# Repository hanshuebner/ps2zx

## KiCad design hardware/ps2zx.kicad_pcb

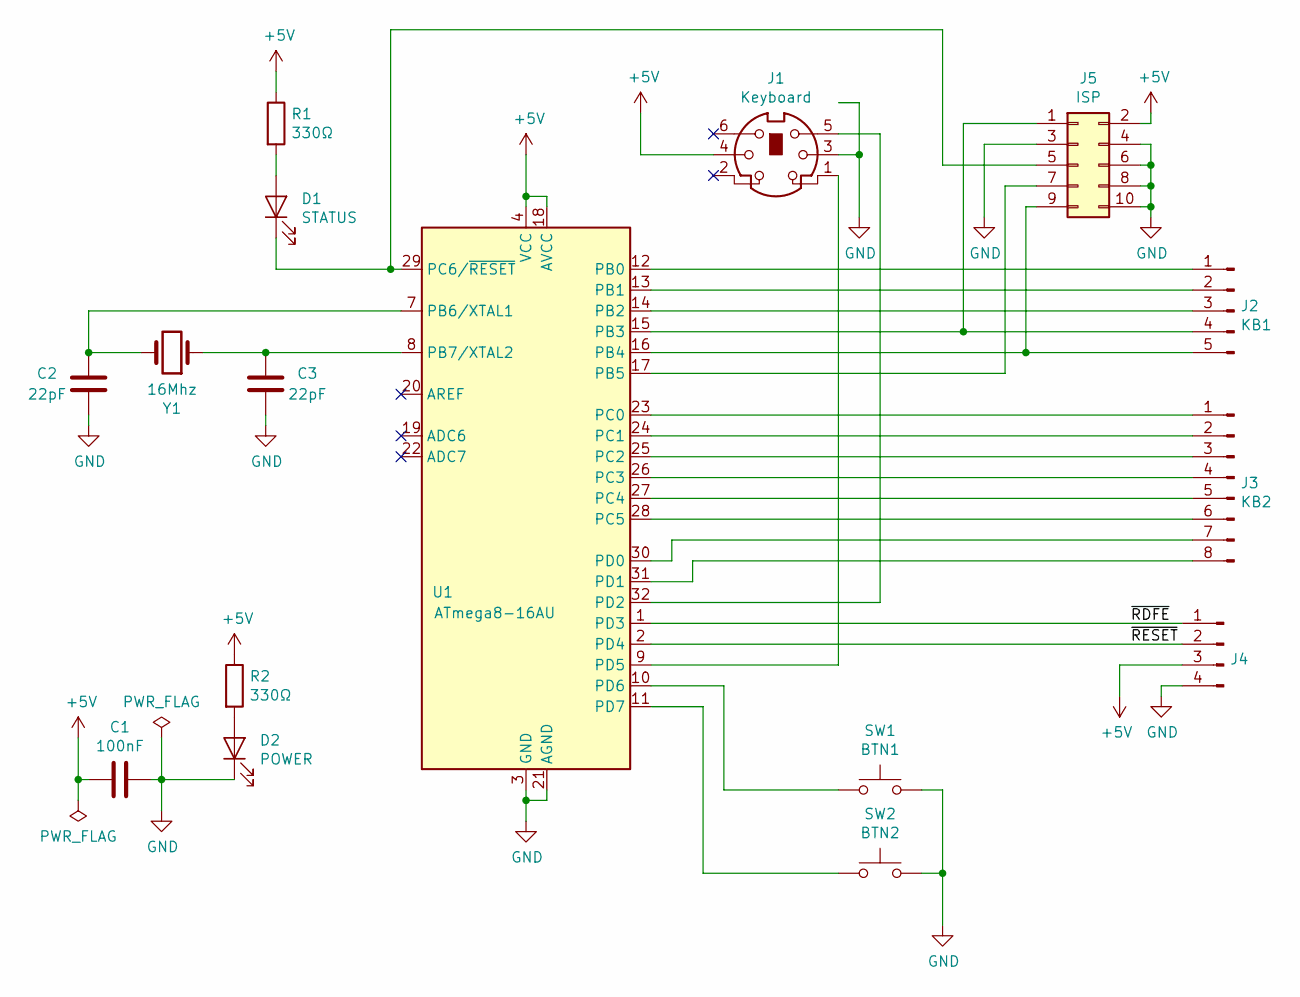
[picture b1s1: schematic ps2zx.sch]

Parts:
C1: 100nF; C_0805_2012Metric_Pad1.15x1.40mm_HandSolder
C2, C3: 22pF; C_0805_2012Metric_Pad1.15x1.40mm_HandSolder
D1: STATUS; LED_0805_2012Metric_Pad1.15x1.40mm_HandSolder
D2: POWER; LED_0805_2012Metric_Pad1.15x1.40mm_HandSolder
J1: Keyboard; Connector_Mini-DIN_Female_6Pin_2rows
J2: KB1; PinHeader_1x05_P2.54mm_Vertical
J3: KB2; PinHeader_1x08_P2.54mm_Vertical
J4: Board; PinHeader_1x04_P2.54mm_Vertical
J5: ISP; PinHeader_2x05_P2.54mm_Vertical
R1, R2: 330Ω; R_0805_2012Metric_Pad1.15x1.40mm_HandSolder
SW1: BTN1; SW_Push_1P1T_NO_6x6mm_H9.5mm
SW2: BTN2; SW_Push_1P1T_NO_6x6mm_H9.5mm
U1: ATmega8-16AU; TQFP-32_7x7mm_P0.8mm
Y1: 16Mhz; Crystal_HC49-U_Vertical

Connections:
+5V: C1.2, J1.4, J4.3, J5.2, R1.1, R2.1, U1.4 (VCC), U1.6 (VCC), U1.18 (AVCC)
/~RDFE: J4.1, U1.1 (PD3)
/~RESET: J4.2, U1.2 (PD4)
GND: C1.1, C2.2, C3.2, D2.1 (K), J1.3, J1.7, J4.4, J5.3, J5.4, J5.6, J5.8, J5.10, SW1.2, SW2.2, U1.3 (GND), U1.5 (GND), U1.21 (AGND)
unnamed: C2.1, U1.7 (PB6/XTAL1), Y1.2
unnamed: C3.1, U1.8 (PB7/XTAL2), Y1.1
unnamed: D1.1 (K), J5.5, U1.29 (PC6/~RESET)
unnamed: D1.2 (A), R1.2
unnamed: D2.2 (A), R2.2
unnamed: J1.1, U1.9 (PD5)
unnamed: J1.5, U1.32 (PD2)
unnamed: J2.1, U1.12 (PB0)
unnamed: J2.2, U1.13 (PB1)
unnamed: J2.3, U1.14 (PB2)
unnamed: J2.4, J5.1, U1.15 (PB3)
unnamed: J2.5, J5.9, U1.16 (PB4)
unnamed: J3.1, U1.23 (PC0)
unnamed: J3.2, U1.24 (PC1)
unnamed: J3.3, U1.25 (PC2)
unnamed: J3.4, U1.26 (PC3)
unnamed: J3.5, U1.27 (PC4)
unnamed: J3.6, U1.28 (PC5)
unnamed: J3.7, U1.30 (PD0)
unnamed: J3.8, U1.31 (PD1)
unnamed: J5.7, U1.17 (PB5)
unnamed: SW1.1, U1.10 (PD6)
unnamed: SW2.1, U1.11 (PD7)

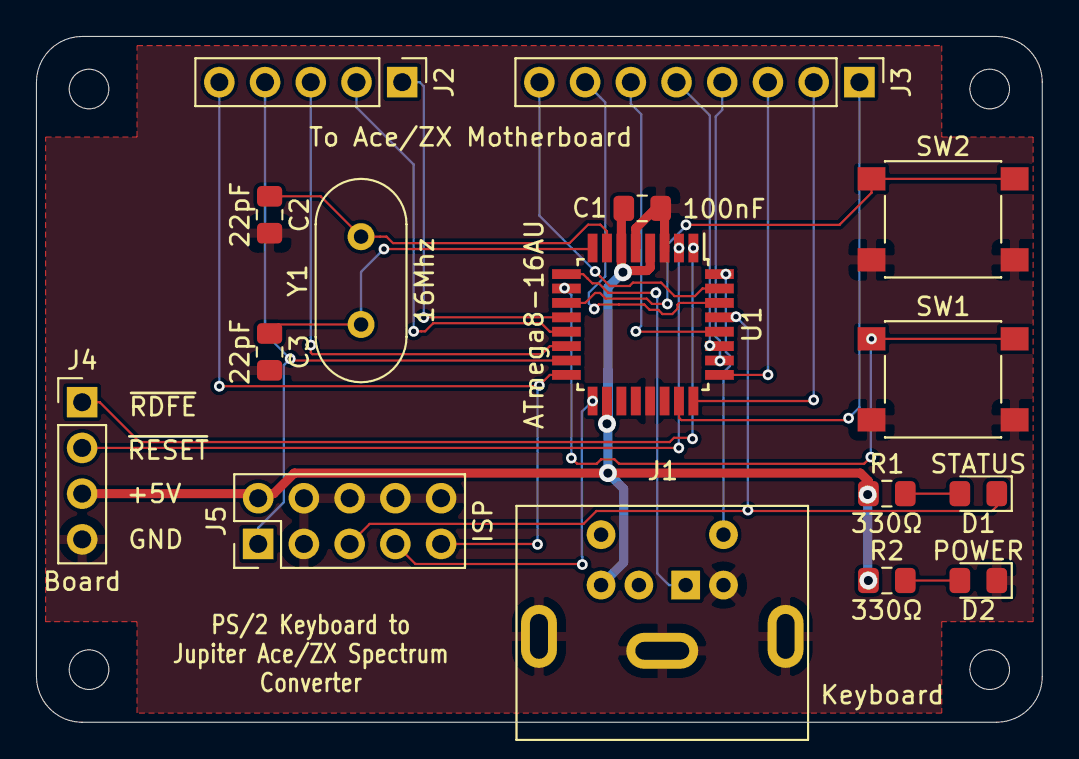
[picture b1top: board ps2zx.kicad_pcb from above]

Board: 2 copper layers, 55.9 x 38.1 mm, 16 parts (0 on the bottom side), 27 nets.

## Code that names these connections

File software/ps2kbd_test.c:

#include "ps2kbd.h"

#include <avr/io.h>
#include <avr/interrupt.h>

int
main()
{
  unsigned char	c;

  kbd_init();

  DDRB |= 0x1F;
  DDRC |= 0x3F;
  DDRD |= 0x03;

  // Enable pull-ups for buttons
  PORTD |= _BV(PD6);
  PORTD |= _BV(PD7);

  // Set ~RESET pin as output
  DDRD |= _BV(PD4);

  sei();

  while(1) {
    PORTD |= _BV(PD4);
    while (c = kbd_getchar()) {
      PORTC = c;
      if (c & 0x40) {
        PORTD |= _BV(PD0);
      } else {
        PORTD &= ~_BV(PD0);
      }
      if (c & 0x80) {
        PORTD |= _BV(PD1);
      } else {
        PORTD &= ~_BV(PD1);
      }
      PORTB = kbd_get_status();
    }
    PORTD &= ~_BV(PD4);
  }
	
  return 0;
}

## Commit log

2020-06-07 Make into separate project
2020-06-20 Revised version (not yet produced)
2020-06-21 Version 4 pre-production
2020-06-21 Test firmware
2020-06-21 .gitignore
2020-06-21 Test program enhanced
2020-06-21 Gerber update
